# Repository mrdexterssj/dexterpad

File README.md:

# Dexterpad

A custom macropad with the looks! Built for Half Life@11/26 #YSWS

## Features

* 9 customizable Cherry MX keys with keycaps
* A rotary encoder (volume and play/pause)
* A 1x4 pinheader to connect a physical button in the future 
* Kmk (circuitpython) firmware
* LEDs to display the current layer (soon)

## Firmware description

The firmware was written in python (circuitpython) using the kmk libraries. This allowed me to easily add features such as keyboard matrix scan, status LEDs, custom keybindings and rotary encoder functionality easily. I also edited one of the built-in extensions to make it work with 4 LEDs instead of 3. The firmware can be found inside /firmware.

## BOM Table

|Item                                          |Qty|Supplier |Cost/item|Total Cost|link                                                                                                                                          |
|----------------------------------------------|---|---------|---------|----------|----------------------------------------------------------------------------------------------------------------------------------------------|
|Waveshare ESP32-S3-Zero                       |1  |Waveshare|$5.49    |$5.49     |https://www.waveshare.com/esp32-s3-zero.htm?sku=25081                                                                                         |
|RotaryEncoder_Alps_EC11E-Switch_Vertical_H20mm|1  |Temu     |$1.21    |$1.21     |https://www.temu.com/ec/1pc-accesorio-de-robot-s----rotatorio-ec11-potenciometro-digital-para-altavoz-con--5-pines-20mm-g-606209147009488.html|
|Estimated total shipping                      |1  |         |         |$10.00    |                                                                                                                                              |

## Screenshots

_Front render_

_Back render_

_PCB_

_Schematic_

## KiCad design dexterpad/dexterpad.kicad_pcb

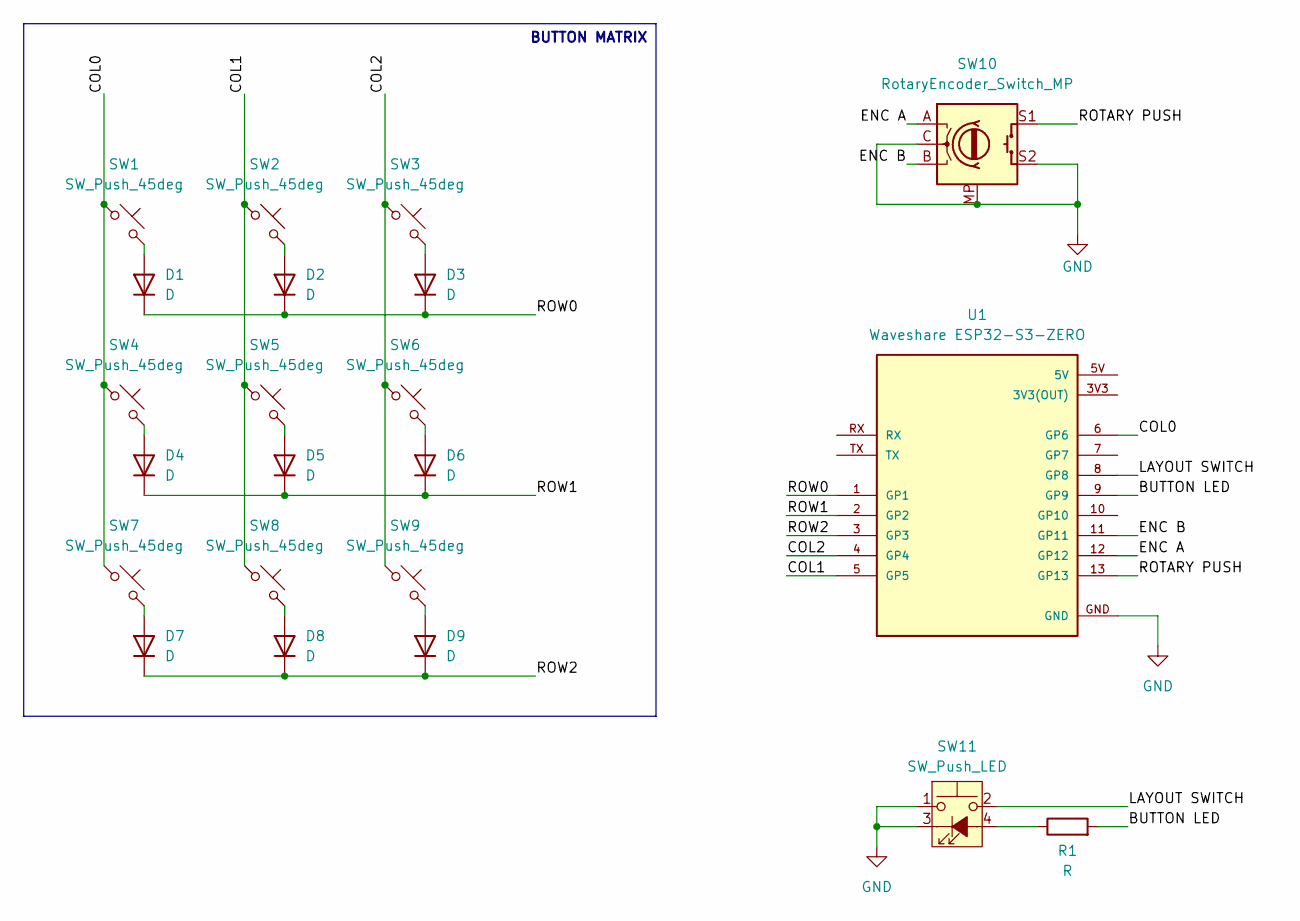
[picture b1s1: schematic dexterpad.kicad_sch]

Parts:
D1, D2, D3, D4, D5, D6, D7, D8, D9: D; D_DO-35_SOD27_P7.62mm_Horizontal
R1: R; R_Axial_DIN0204_L3.6mm_D1.6mm_P7.62mm_Horizontal
SW1, SW2, SW3, SW4, SW5, SW6, SW7, SW8, SW9: SW_Push_45deg; SW_Cherry_MX_1.00u_PCB
SW10: RotaryEncoder_Switch_MP; RotaryEncoder_Alps_EC11E-Switch_Vertical_H20mm
SW11: SW_Push_LED; PinHeader_1x04_P2.54mm_Vertical
U1: Waveshare ESP32-S3-ZERO; Waveshare ESP32-S3-Zero; PARTREV NA

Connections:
/BUTTON LED: R1.2, U1.9 (GP9)
/COL0: SW1.1, SW4.1, SW7.1, U1.6 (GP6)
/COL1: SW2.1, SW5.1, SW8.1, U1.5 (GP5)
/COL2: SW3.1, SW6.1, SW9.1, U1.4 (GP4)
/ENC A: SW10.A, U1.12 (GP12)
/ENC B: SW10.B, U1.11 (GP11)
/LAYOUT SWITCH: SW11.2, U1.8 (GP8)
/ROTARY PUSH: SW10.S1, U1.13 (GP13)
/ROW0: D1.1 (K), D2.1 (K), D3.1 (K), U1.1 (GP1)
/ROW1: D4.1 (K), D5.1 (K), D6.1 (K), U1.2 (GP2)
/ROW2: D7.1 (K), D8.1 (K), D9.1 (K), U1.3 (GP3)
GND: SW10.C, SW10.MP, SW10.S2, SW11.1, SW11.3 (K), U1.GND
unnamed: D1.2 (A), SW1.2
unnamed: D2.2 (A), SW2.2
unnamed: D3.2 (A), SW3.2
unnamed: D4.2 (A), SW4.2
unnamed: D5.2 (A), SW5.2
unnamed: D6.2 (A), SW6.2
unnamed: D7.2 (A), SW7.2
unnamed: D8.2 (A), SW8.2
unnamed: D9.2 (A), SW9.2
unnamed: R1.1, SW11.4 (A)

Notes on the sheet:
BUTTON MATRIX

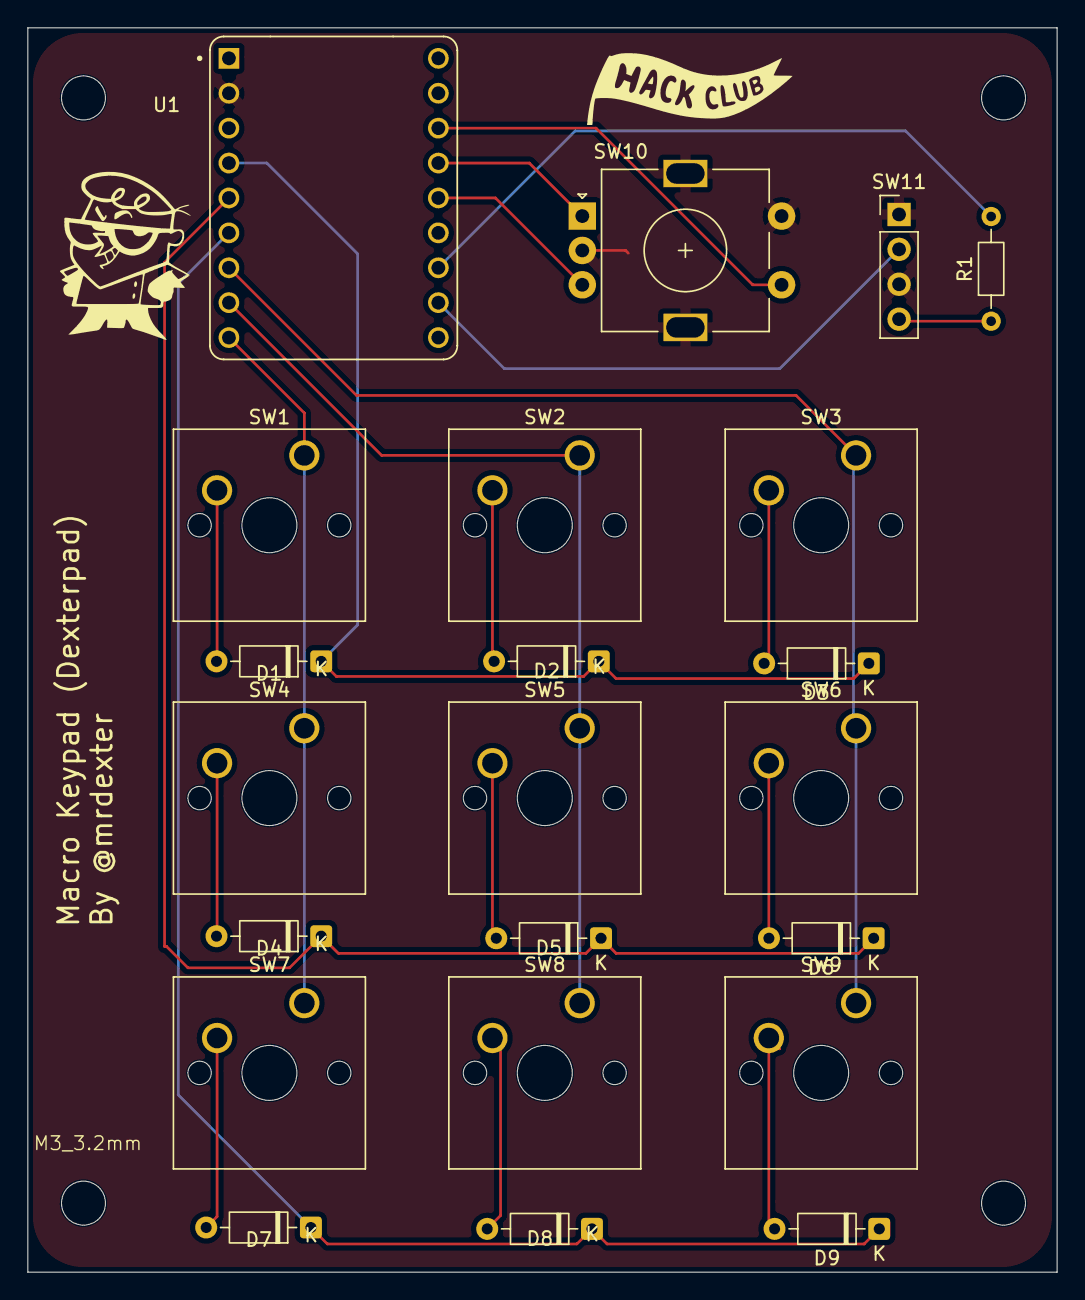
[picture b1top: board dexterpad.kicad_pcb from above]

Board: 2 copper layers, 74.9 x 90.6 mm, 22 parts (0 on the bottom side), 22 nets.
